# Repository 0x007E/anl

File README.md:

# `ANL` - AND Logic Board

The `ANL` is a board with an [CD4081](#additional-information) or any other 4-channel `AND` gate driver that meets the pin requirements. The board itself can be driven from `5` to `15V`. The board offers the possibility to `AND` signals from buttons, switches or any other logic board.

| Experience  | Level                                                                               |
|:------------|:-----------------------------------------------------------------------------------:|
| Soldering   |  |

# Downloads

| Type      | File                                                                                                                                                 | Description     |
|:---------:|:----------------------------------------------------------------------------------------------------------------------------------------------------:|:----------------|
| Schematic | [pdf](https://github.com/0x007E/anl/releases/latest/download/schematic.pdf) / [cadlab](https://cadlab.io/project/30125/main/files)                   | Schematic files |
| Board     | [pdf](https://github.com/0x007E/anl/releases/latest/download/pcb.pdf) / [cadlab](https://cadlab.io/project/30125/main/files)                         | Board file      |
| Drill     | [pdf](https://github.com/0x007E/anl/releases/latest/download/drill.pdf)                                                                              | Drill file      |
| PCB       | [zip](https://github.com/0x007E/anl/releases/latest/download/kicad.zip) / [tar](https://github.com/0x007E/anl/releases/latest/download/kicad.tar.gz) | KiCAD/Gerber/BoM/Drill files |
| Mechanical | [zip](https://github.com/0x007E/anl/releases/latest/download/freecad.zip) / [tar](https://github.com/0x007E/anl/releases/latest/download/freecad.tar.gz) | FreeCAD/Housing and exported step/stl files |

# Hardware

The pcb is created with `KiCAD`. All files are built with `github actions` so that they are ready for a production environment.

## PCB

The circuit board is populated on both sides (Top, Bottom). The best way for soldering the `SMD` components is within a vapor phase soldering system and for the `THT` components with a standard soldering system.

### Top Layer

### Bottom Layer

# Additional Information

| Type       | Link                                                  | Description                                 |
|:----------:|:-----------------------------------------------------:|:--------------------------------------------|
| CD4081    | [pdf](https://www.ti.com/lit/ds/symlink/cd4081b.pdf)   | CMOS AND Gate                               |

---

R. GAECHTER

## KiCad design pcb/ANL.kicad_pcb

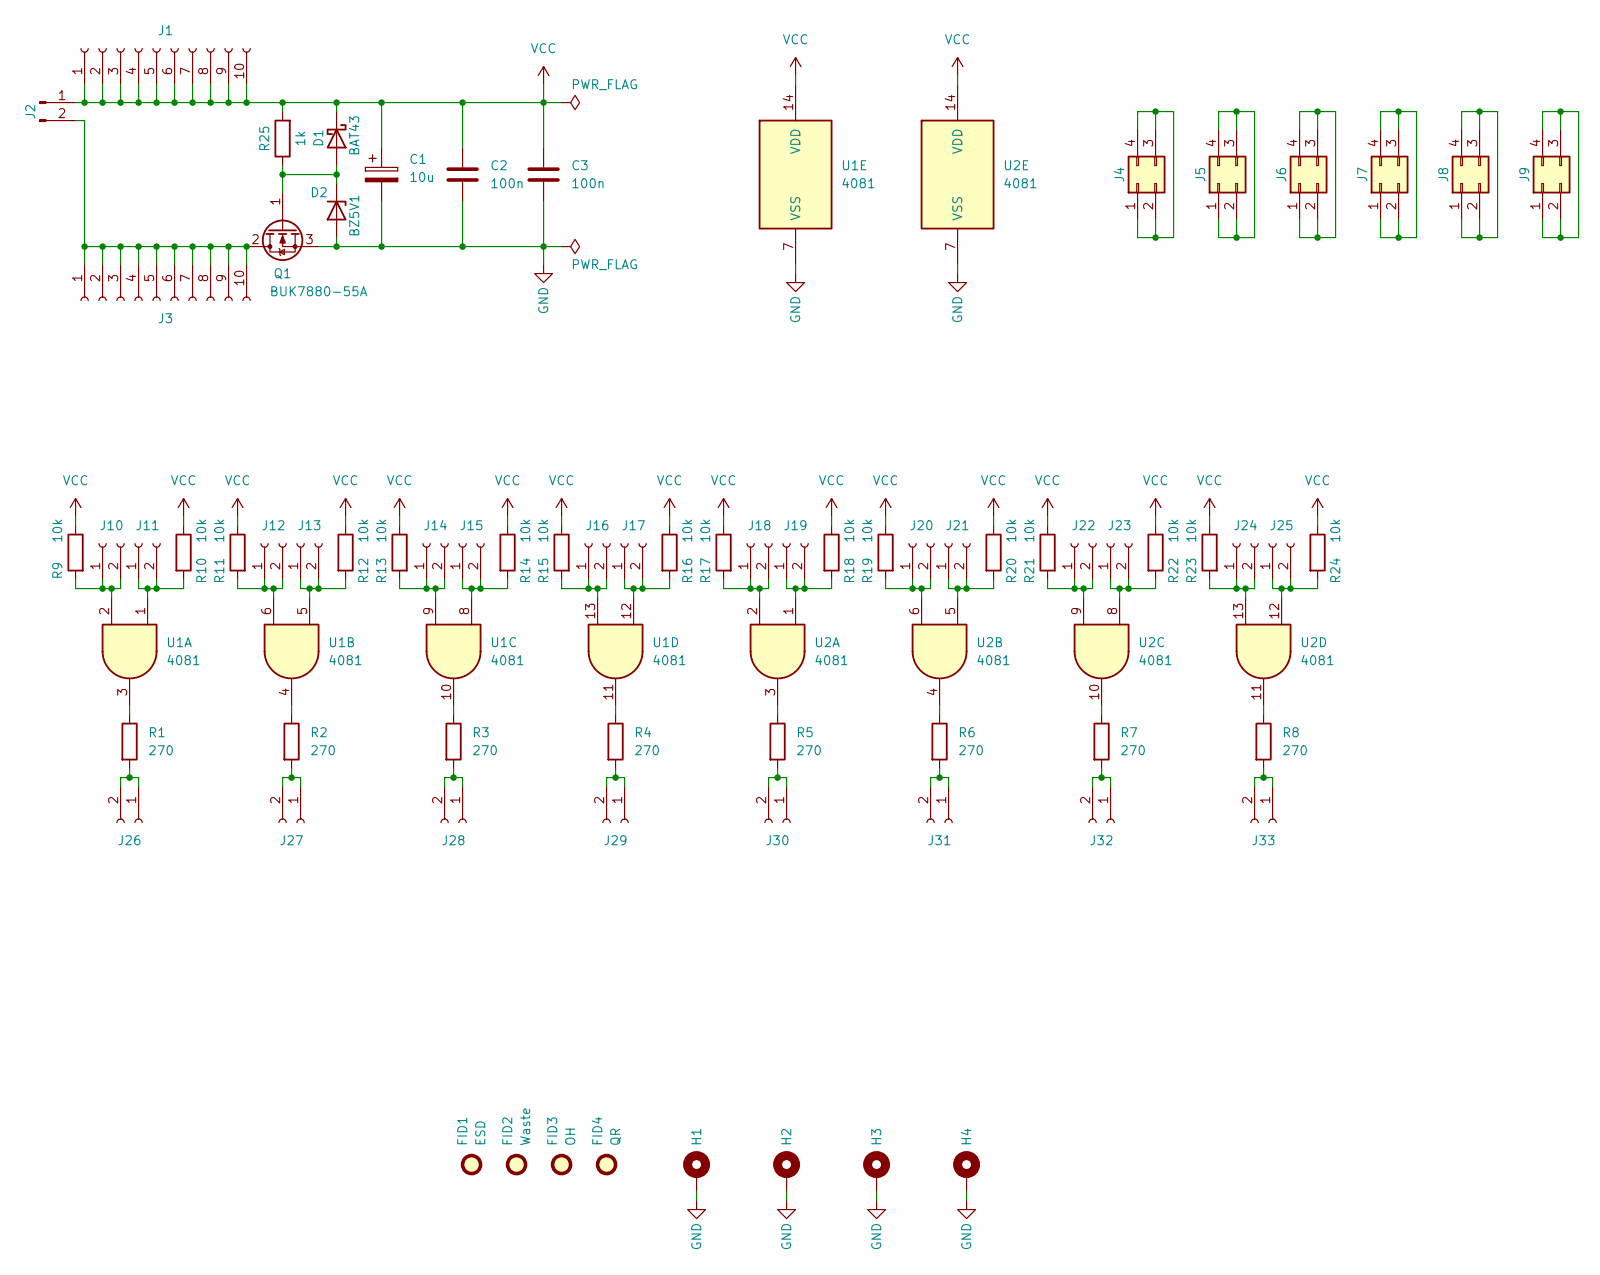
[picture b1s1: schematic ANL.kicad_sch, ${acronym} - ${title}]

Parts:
C1: 10u; CP_Radial_D6.3mm_P2.50mm
C2, C3: 100n; C_1206_3216Metric
D1: BAT43; D_MiniMELF
D2: BZ5V1; D_MiniMELF
FID1: ESD; ESD-Logo_6.6x6mm_SilkScreen
FID2: Waste; WEEE-Logo_4.2x6mm_SilkScreen
FID3: OH; OSHW-Logo_5.7x6mm_SilkScreen
FID4: QR; QR_0x007e
H1, H2, H3, H4: MountingHole_Pad; MountingHole_3.2mm_M3_Pad
J1, J3: Conn_01x10_Socket; PinSocket_1x10_P2.54mm_Vertical
J2: Conn_01x02_Pin; PinHeader_1x02_P2.54mm_Vertical
J4, J5, J6, J7, J8, J9: Conn_02x02_Counter_Clockwise; PinSocket_2x02_P2.54mm_Vertical
J10, J11, J12, J13, J14, J15, J16, J17, J18, J19, J20, J21, J22, J23, J24, J25, J26, J27, J28, J29, J30, J31, J32, J33: Conn_01x02_Socket; PinSocket_1x02_P2.54mm_Vertical
Q1: BUK7880-55A; SOT-223-3_TabPin2
R1, R2, R3, R4, R5, R6, R7, R8: 270; R_1206_3216Metric
R9, R10, R11, R12, R13, R14, R15, R16, R17, R18, R19, R20, R21, R22, R23, R24: 10k; R_1206_3216Metric
R25: 1k; R_1206_3216Metric
U1, U2: 4081; SOIC-14_3.9x8.7mm_P1.27mm

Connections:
GND: C1.2, C2.2, C3.2, D2.2 (A), H1.1, H2.1, H3.1, H4.1, Q1.3 (S), U1.7 (VSS), U2.7 (VSS)
unnamed: D1.2 (A), D2.1 (K), Q1.1 (G), R25.1
unnamed: J2.2, J3.1, J3.2, J3.3, J3.4, J3.5, J3.6, J3.7, J3.8, J3.9, J3.10, Q1.2 (D)
unnamed: J4.1, J4.2, J4.3, J4.4
unnamed: J5.1, J5.2, J5.3, J5.4
unnamed: J6.1, J6.2, J6.3, J6.4
unnamed: J7.1, J7.2, J7.3, J7.4
unnamed: J8.1, J8.2, J8.3, J8.4
unnamed: J9.1, J9.2, J9.3, J9.4
unnamed: J10.1, J10.2, R9.2, U1.2
unnamed: J11.1, J11.2, R10.2, U1.1
unnamed: J12.1, J12.2, R11.2, U1.6
unnamed: J13.1, J13.2, R12.2, U1.5
unnamed: J14.1, J14.2, R13.2, U1.9
unnamed: J15.1, J15.2, R14.2, U1.8
unnamed: J16.1, J16.2, R15.2, U1.13
unnamed: J17.1, J17.2, R16.2, U1.12
unnamed: J18.1, J18.2, R17.2, U2.2
unnamed: J19.1, J19.2, R18.2, U2.1
unnamed: J20.1, J20.2, R19.2, U2.6
unnamed: J21.1, J21.2, R20.2, U2.5
unnamed: J22.1, J22.2, R21.2, U2.9
unnamed: J23.1, J23.2, R22.2, U2.8
unnamed: J24.1, J24.2, R23.2, U2.13
unnamed: J25.1, J25.2, R24.2, U2.12
unnamed: J26.1, J26.2, R1.2
unnamed: J27.1, J27.2, R2.2
unnamed: J28.1, J28.2, R3.2
unnamed: J29.1, J29.2, R4.2
unnamed: J30.1, J30.2, R5.2
unnamed: J31.1, J31.2, R6.2
unnamed: J32.1, J32.2, R7.2
unnamed: J33.1, J33.2, R8.2
unnamed: R1.1, U1.3
unnamed: R2.1, U1.4
unnamed: R3.1, U1.10
unnamed: R4.1, U1.11
unnamed: R5.1, U2.3
unnamed: R6.1, U2.4
unnamed: R7.1, U2.10
unnamed: R8.1, U2.11
VCC: C1.1, C2.1, C3.1, D1.1 (K), J1.1, J1.2, J1.3, J1.4, J1.5, J1.6, J1.7, J1.8, J1.9, J1.10, J2.1, R9.1, R10.1, R11.1, R12.1, R13.1, R14.1, R15.1, R16.1, R17.1, R18.1, R19.1, R20.1, R21.1, R22.1, R23.1, R24.1, R25.2, U1.14 (VDD), U2.14 (VDD)

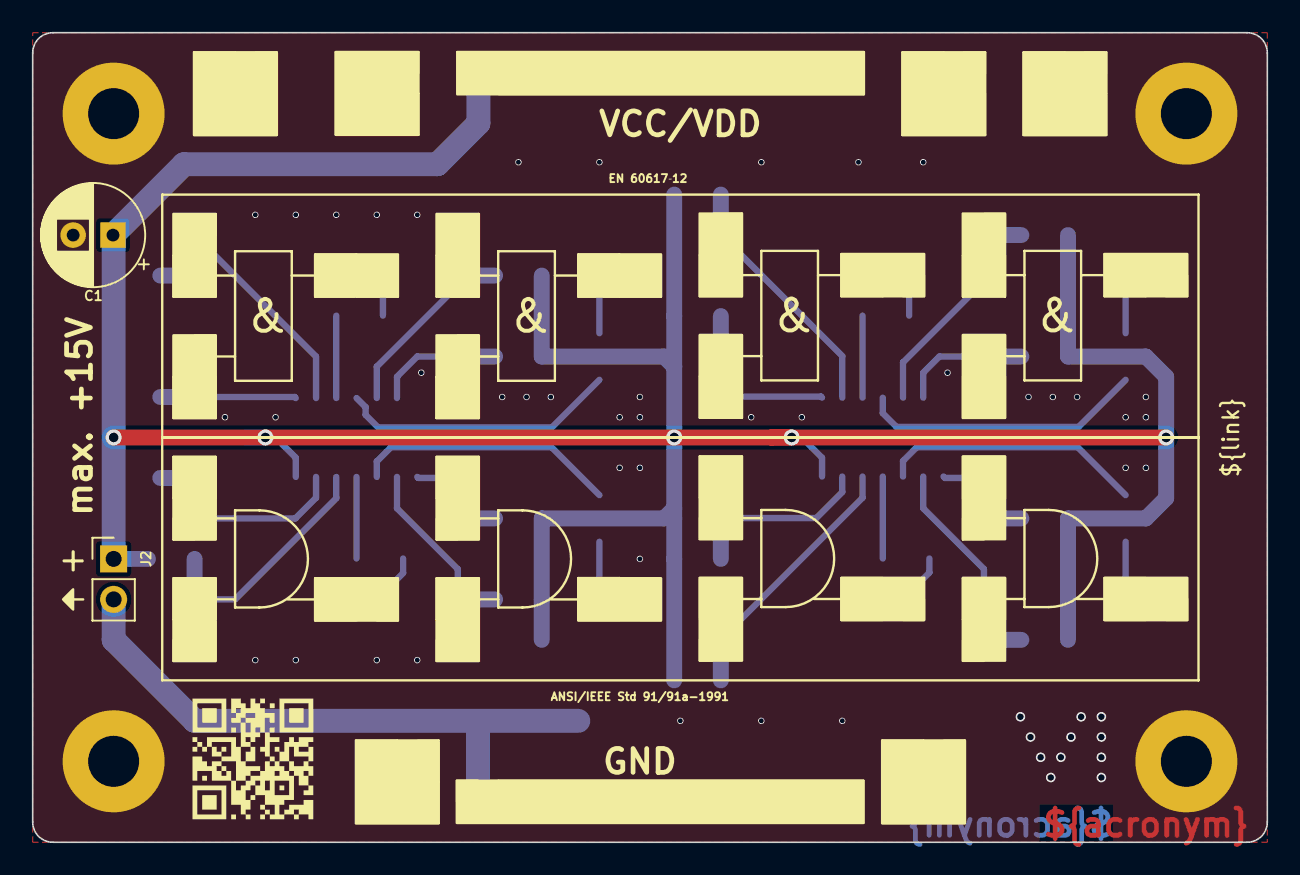
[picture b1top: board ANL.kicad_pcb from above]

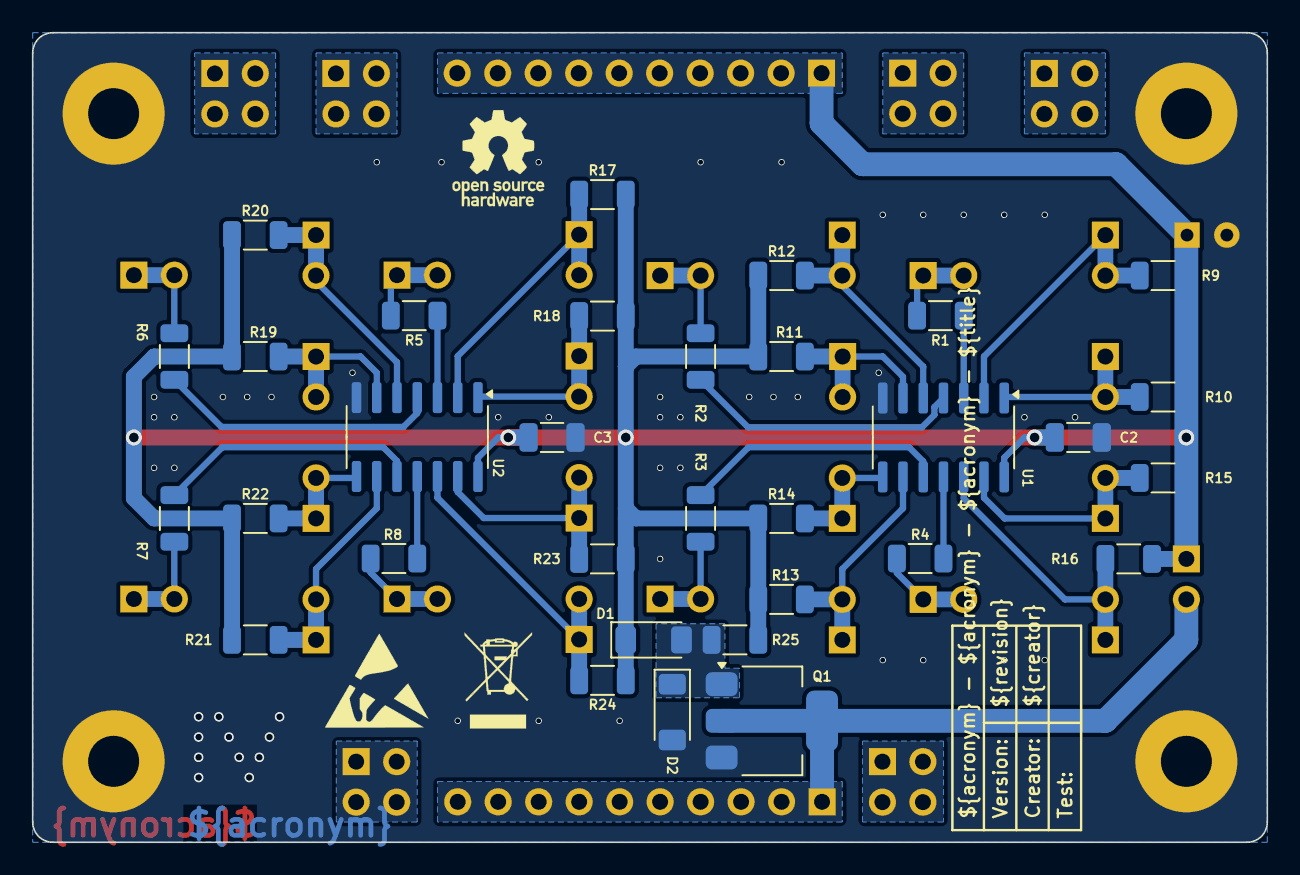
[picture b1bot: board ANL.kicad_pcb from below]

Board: 2 copper layers, 77.5 x 50.8 mm, 74 parts (35 on the bottom side), 42 nets.

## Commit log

2026-03-03 Add pcb layout
2026-03-03 Add README.md
2026-03-03 Add build pipeline
2026-03-03 Add release pipeline
2026-03-03 Add missing vendor
2026-03-09 Remove invalid text
2026-03-21 Fix heading title
2026-03-23 Adapt edge cuts and dimensioning
2026-03-23 Add mechanical download link
2026-03-23 Add FreeCAD modification and export
2026-05-09 Add reverse polarity protection
2026-05-09 Remove isolated copper filter
2026-05-11 Optimize fabrication layer
2026-05-12 Adapt description

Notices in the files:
README.md:
License CC By-NC-SA
parts and their libraries:
license: CC BY-NC-SA 4.0
